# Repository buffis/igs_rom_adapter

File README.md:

# IGS/Everstar ROM Adapter

Simple adapter for dumping IGS/Everstar EV29LV160 and EV29LV640 ROMs with any programmer supporting M27V322 EPROMs.

These ROMs appear on IGS-made boards, and are not supported by most programmers.

Note that these ROMs are 3.3V. Make sure your programmer uses 3.3V supply voltage for M27V322. 

Gerbers ready for fabrication is available in adapter/gerber/gerber.zip

## BOM

- 1x 42pin DIP socket
- 2x 24pin DIP sockets
- 2x 01x21 2.54mm pin header
- 1x 01x03 2.54mm pin header
- 1x 2.54mm jumper
- 5x through-hole resistors (value not very important, I used 100ohm)

## Build instructions

1. Mount 42pin DIP socket on the EV29LV160 position.
2. Mount 2x 24pin DIP sockets on the EV29LV640 position.
3. Mount 2x 21pin headers on the underside of the board at the M27V322 position.
4. Mount 3pin header at the A21 position. Attach a jumper between center pin and 0.
5. Mount 5x pull-up resistors.

Should end up looking like this:

## Dumping EV29LV160

1. Insert EV29LV160 into the socket marked for it.
2. Dump as M27V322
3. Ignore any error about pin 32 not being connected.
4. This will dump to a file of size 0x400000, containing the same data twice.
5. Discard the duplicate data from 0x200000 to the end of file.
6. The remaining data (size 0x200000) contains the dump.

## Dumping EV29LV640

1. Insert EV29LV640 into the socket marked for it.
2. Make sure the A21 jumper ties the center pin with the pin marked 0.
3. Dump as M27V322, save to a file 0.bin.
4. Move jumped to tie center pin with pin marked 1.
5. Dump as M27V322, save to a file 1.bin.
6. Concatenate the two files. 0.bin first, then 1.bin directly after that data.
7. The merged data (size 0x800000) contains the dump.

## Schematic and Board layout

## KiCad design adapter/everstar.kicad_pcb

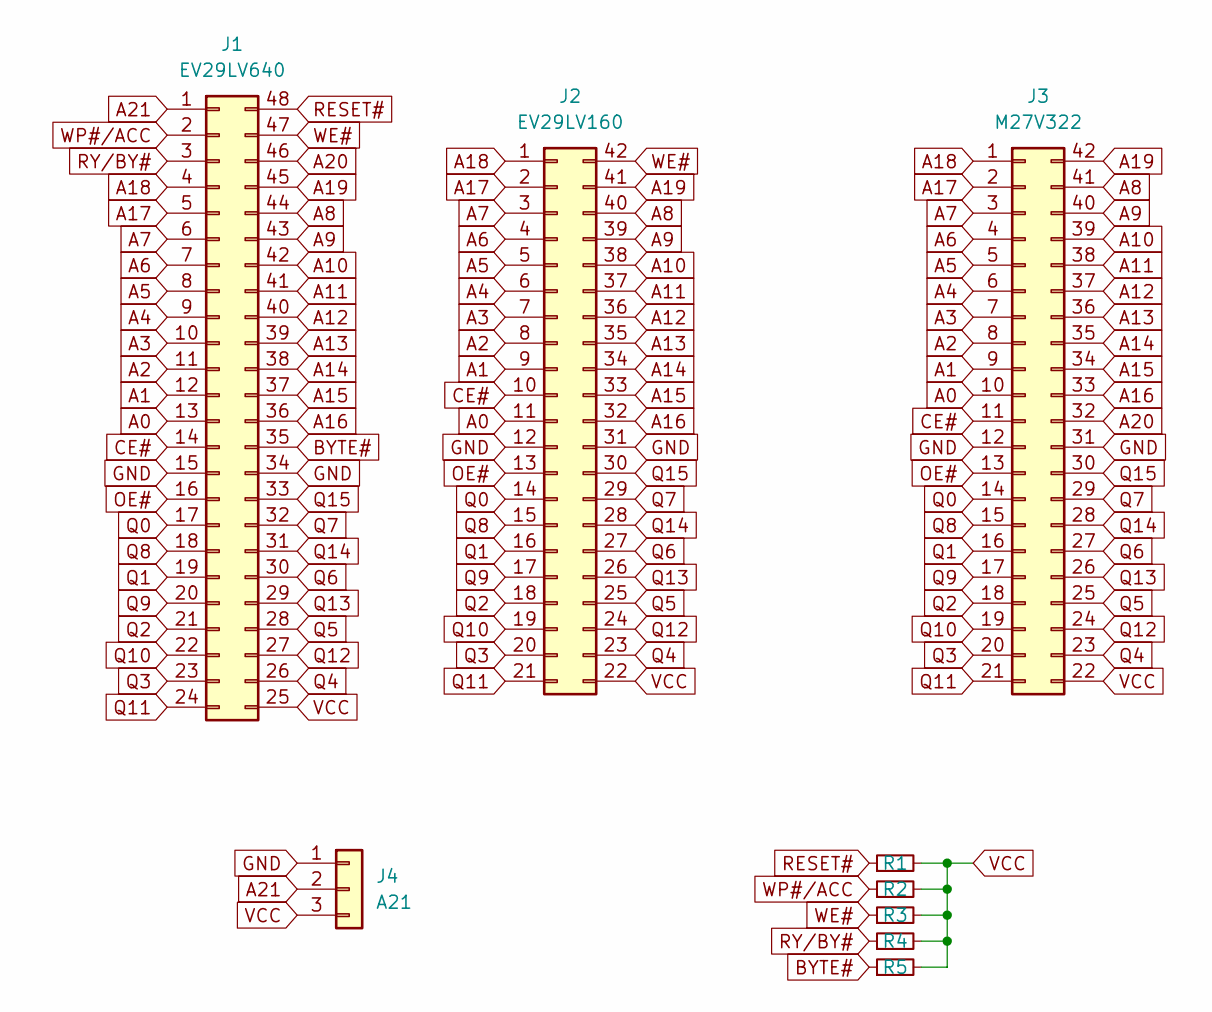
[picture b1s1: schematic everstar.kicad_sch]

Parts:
J1: EV29LV640; DIP-48_W15.24mm_Socket
J2: EV29LV160; DIP-42_W15.24mm_Socket
J3: M27V322; DIP-42_W15.24mm_Socket
J4: A21; PinHeader_1x03_P2.54mm_Vertical
R1, R2, R3, R4, R5: R_Small; R_Axial_DIN0207_L6.3mm_D2.5mm_P10.16mm_Horizontal

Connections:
A0: J1.13, J2.11, J3.10
A1: J1.12, J2.9, J3.9
A2: J1.11, J2.8, J3.8
A3: J1.10, J2.7, J3.7
A4: J1.9, J2.6, J3.6
A5: J1.8, J2.5, J3.5
A6: J1.7, J2.4, J3.4
A7: J1.6, J2.3, J3.3
A8: J1.44, J2.40, J3.41
A9: J1.43, J2.39, J3.40
A10: J1.42, J2.38, J3.39
A11: J1.41, J2.37, J3.38
A12: J1.40, J2.36, J3.37
A13: J1.39, J2.35, J3.36
A14: J1.38, J2.34, J3.35
A15: J1.37, J2.33, J3.34
A16: J1.36, J2.32, J3.33
A17: J1.5, J2.2, J3.2
A18: J1.4, J2.1, J3.1
A19: J1.45, J2.41, J3.42
A20: J1.46, J3.32
A21: J1.1, J4.2
BYTE#: J1.35, R5.1
CE#: J1.14, J2.10, J3.11
GND: J1.15, J1.34, J2.12, J2.31, J3.12, J3.31, J4.1
OE#: J1.16, J2.13, J3.13
Q0: J1.17, J2.14, J3.14
Q1: J1.19, J2.16, J3.16
Q2: J1.21, J2.18, J3.18
Q3: J1.23, J2.20, J3.20
Q4: J1.26, J2.23, J3.23
Q5: J1.28, J2.25, J3.25
Q6: J1.30, J2.27, J3.27
Q7: J1.32, J2.29, J3.29
Q8: J1.18, J2.15, J3.15
Q9: J1.20, J2.17, J3.17
Q10: J1.22, J2.19, J3.19
Q11: J1.24, J2.21, J3.21
Q12: J1.27, J2.24, J3.24
Q13: J1.29, J2.26, J3.26
Q14: J1.31, J2.28, J3.28
Q15: J1.33, J2.30, J3.30
RESET#: J1.48, R1.1
RY/BY#: J1.3, R4.1
VCC: J1.25, J2.22, J3.22, J4.3, R1.2, R2.2, R3.2, R4.2, R5.2
WE#: J1.47, J2.42, R3.1
WP#/ACC: J1.2, R2.1

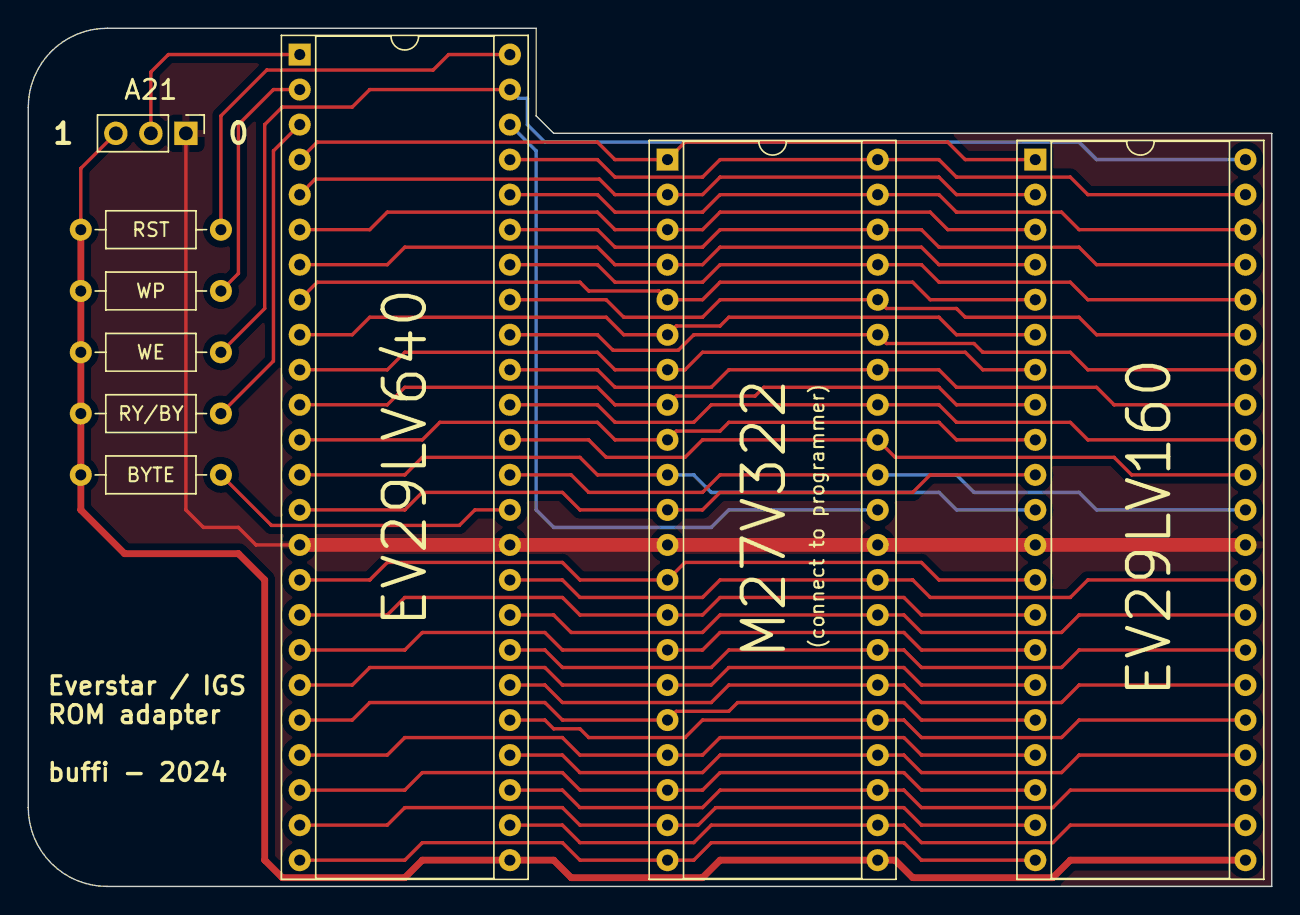
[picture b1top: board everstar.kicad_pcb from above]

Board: 2 copper layers, 90.2 x 62.2 mm, 9 parts (0 on the bottom side), 47 nets.

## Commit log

2023-12-17 Add Kicad files
2023-12-17 Add docs
2023-12-17 Order number position on bottom layer for JLCPCB
2024-01-04 minor cleanups
2024-01-04 Add pics
